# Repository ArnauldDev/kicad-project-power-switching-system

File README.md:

# Power switching system

Realization of a power supply board with four switches for switching between several power sources.

## Check list

- [x] Analysis of the specifications
- [x] Choice of components and case
- [x] Order components
- [x] Validation of the schematic
- [x] Definition of the PCB outline from the internal dimensions of the case
- [x] Validate component placement and lock footprints
- [x] Routing validation
- [x] Screen printing validation
- [x] Generating design files
- [x] Assembly of components on the PCB
- [x] Functional test of the electronic board and validation of the specifications
- [x] Integration of the electronic card in the case
- [x] Final test and document review
- [ ] Device delivery

---

## Tools used

### KiCad

[KiCad EDA - Schematic Capture & PCB Design Software](https://kicad-pcb.org/), version: 5.1.7

Open source EDA / electronics CAD software for Windows, macOS and Linux.

### FreeCAD - 3D parametric modeler

[FreeCAD](https://www.freecadweb.org/?lang=fr), version: 0.18.4

## Electrical diagram

---

## Integration into the housing

[Hammond 1599HGYBAT](https://www.hammfg.com/part/1599HGYBAT)

Enclosure - plastic, size: 220 mm x 110 mm x 44 mm (L x W x H)

## PCB outline, size: 213,00 mm x 96,60 mm (L x W), from FreeCAD

## Component placement and silk screen

|                        Placement                         |                      Silk screen                      |
| :------------------------------------------------------: | :---------------------------------------------------: |
|  |  |
|           F.Mask + Edge.Cuts + F.CrtYd + F.Fab           |                  F.SilkS + Edge.Cuts                  |

|                      Placement and Silk screen                      |
| :-----------------------------------------------------------------: |
|  |
|           F.SilkS + F.Mask + Edge.Cuts + F.CrtYd + F.Fab            |

<!--
### Component placement - Component layout

F.Mask + Edge.Cuts + F.CrtYd + F.Fab

### Silk screen

F.SilkS + Edge.Cuts
-->

## Top - Front Copper layer

<!--  -->

## Bottom - Back Copper layer

<!--  -->

<!-- ## Component layout

pcb-component-placement.pdf
 -->

## 3D rendering

## Integration of the electronic card in the case with the [FreeCAD](https://www.freecadweb.org) software

## Sectional view

## View of final STEP file for CNC

---

## [CHANGELOG](CHANGELOG.md)

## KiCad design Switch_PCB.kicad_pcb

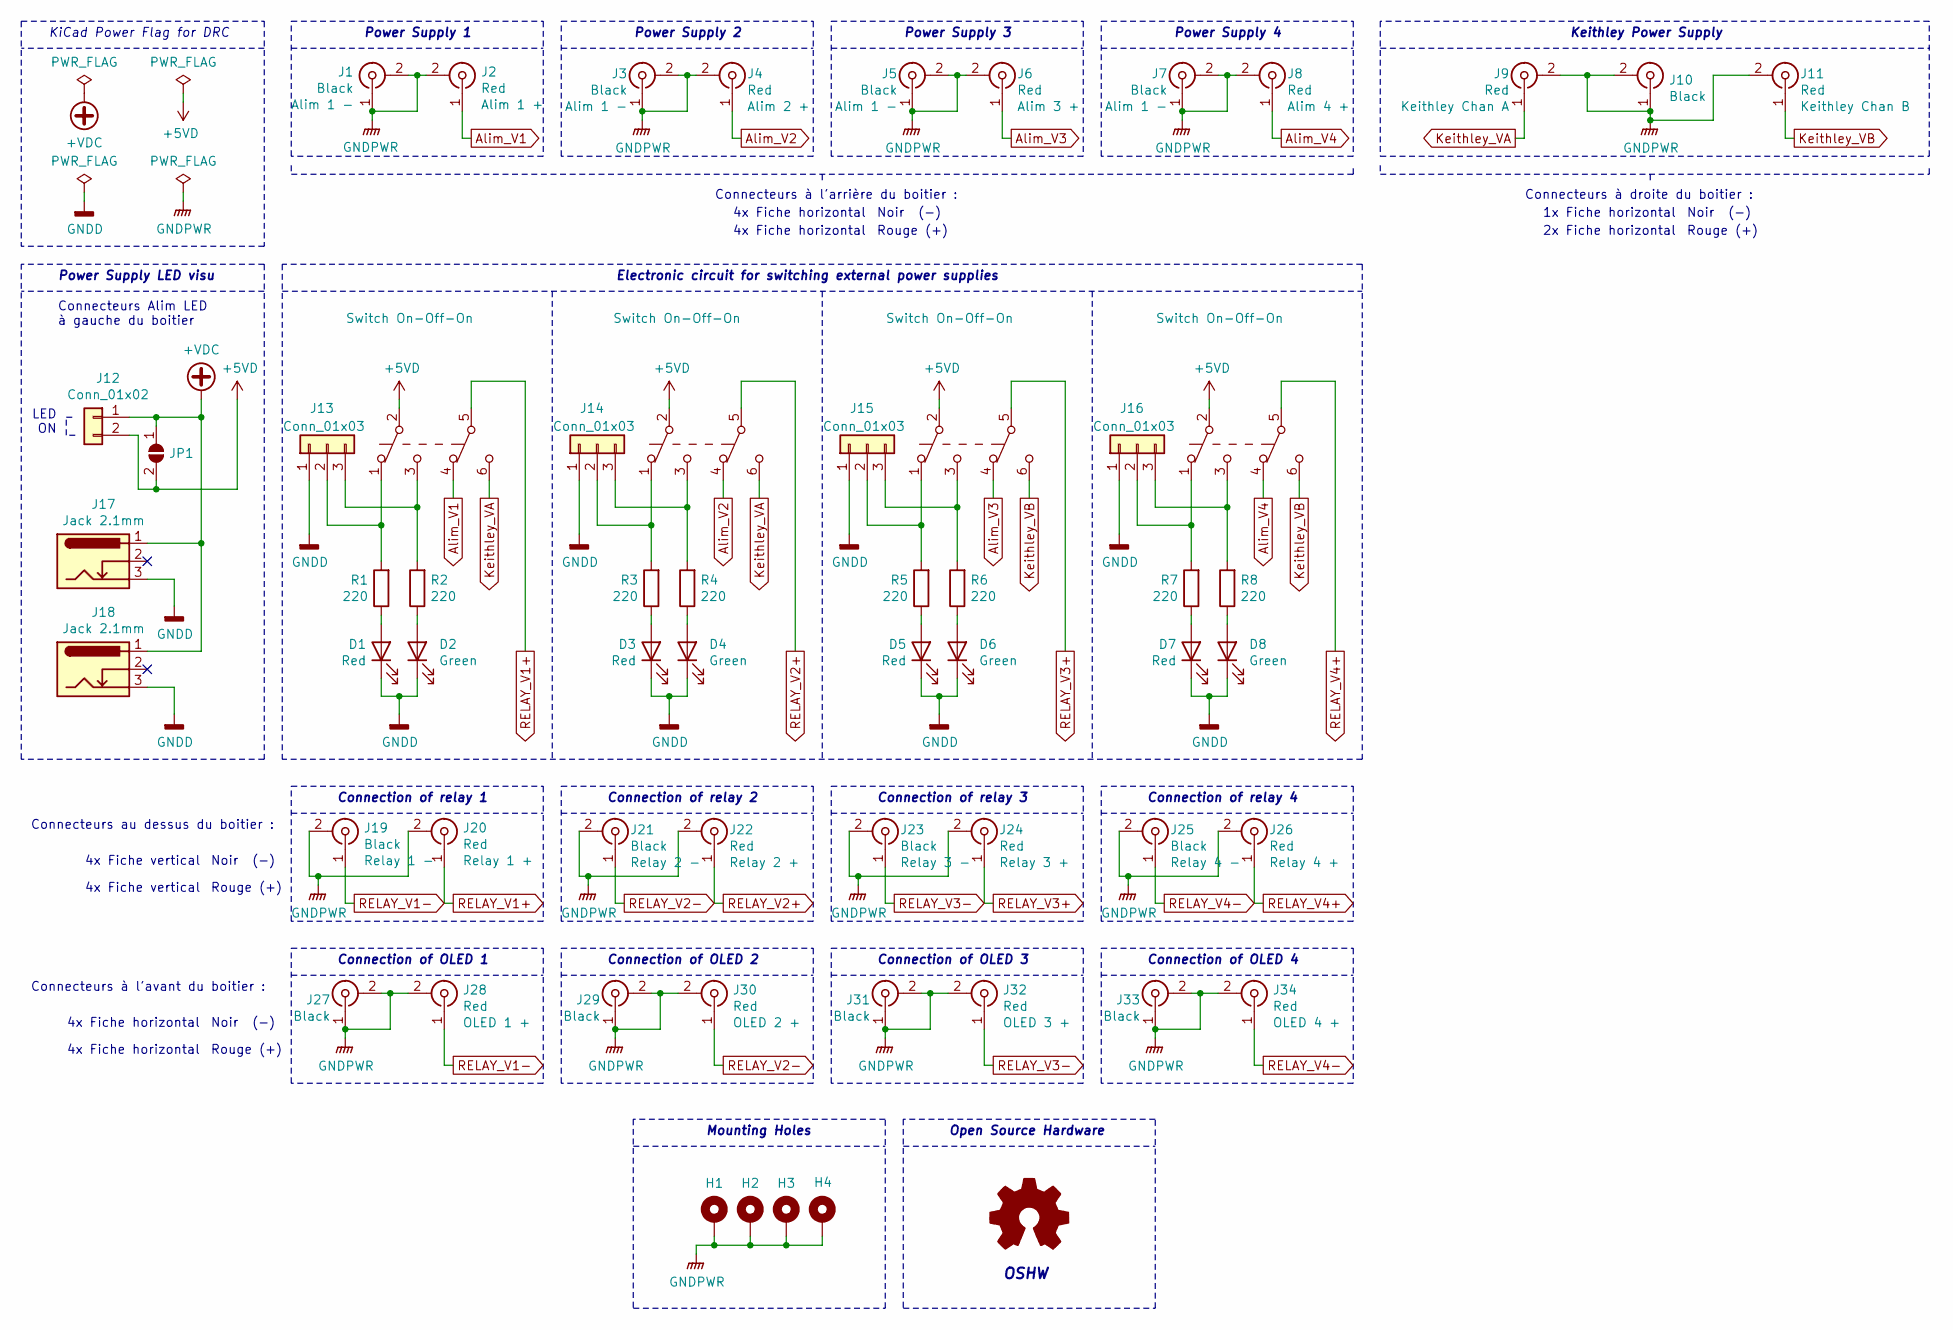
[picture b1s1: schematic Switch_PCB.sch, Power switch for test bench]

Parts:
D1, D3, D5, D7: Red; LED_D3.0mm_H18.0mm_Red; Manufacturer Part Number L-934ID
D2, D4, D6, D8: Green; LED_D3.0mm_H18.0mm_Green; Manufacturer Part Number L-934GD
H1, H2, H3, H4: MountingHole_Pad; MountingHole_3.2mm_M3_Pad
J1, J3, J5, J7, J10, J27, J29, J31, J33: Black; SCHUTZINGER_SWEB8094AU-SW_4mm_Horizontal_Black; Manufacturer Part Number SWEB 8094 Au / SW
J2, J4, J6, J8, J9, J11, J28, J30, J32, J34: Red; SCHUTZINGER_SWEB8094AU-RT_4mm_Horizontal_Red; Manufacturer Part Number SWEB 8094 Au / RT
J12: Conn_01x02; PinHeader_1x02_P2.54mm_Horizontal
J13, J14, J15, J16: Conn_01x03; PinHeader_1x03_P2.54mm_Vertical
J17, J18: Jack 2.1mm; BarrelJack_FC681465P_Pin3_Horizontal; Manufacturer Part Number FC681465P (DC-10LP)
J19, J21, J23, J25: Black; STAUBLI_66.9032-21_XELA-4_4mm_Vertical_Black; Manufacturer Part Number 66.9032-21
J20, J22, J24, J26: Red; STAUBLI_66.9032-22_XELA-4_4mm_Vertical_Red; Manufacturer Part Number 66.9032-22
JP1: SolderJumper_2_Open; SolderJumper-2_P1.3mm_Open_TrianglePad1.0x1.5mm
R1, R2, R3, R4, R5, R6, R7, R8: 220; R_1206_3216Metric_Pad1.30x1.75mm_HandSolder; Manufacturer Part Number CRG1206F220R
SW1, SW2, SW3, SW4: Switch On-Off-On; SW_TME_1MD3T1B1M1QE_DPDT_Straight; Manufacturer Part Number 1MD3T1B1M1QE

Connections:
+5VD: J12.2, JP1.2 (B), SW1.2 (B), SW2.2 (B), SW3.2 (B), SW4.2 (B)
+VDC: J12.1, J17.1, J18.1, JP1.1 (A)
Alim_V1: J2.1 (In), SW1.4 (A)
Alim_V2: J4.1 (In), SW2.4 (A)
Alim_V3: J6.1 (In), SW3.4 (A)
Alim_V4: J8.1 (In), SW4.4 (A)
GNDD: D1.1 (K), D2.1 (K), D3.1 (K), D4.1 (K), D5.1 (K), D6.1 (K), D7.1 (K), D8.1 (K), J13.1, J14.1, J15.1, J16.1, J17.3, J18.3
GNDPWR: H1.1, H2.1, H3.1, H4.1, J1.1 (In), J1.2 (Ext), J2.2 (Ext), J3.1 (In), J3.2 (Ext), J4.2 (Ext), J5.1 (In), J5.2 (Ext), J6.2 (Ext), J7.1 (In), J7.2 (Ext), J8.2 (Ext), J9.2 (Ext), J10.1 (In), J10.2 (Ext), J11.2 (Ext), J19.2 (Ext), J20.2 (Ext), J21.2 (Ext), J22.2 (Ext), J23.2 (Ext), J24.2 (Ext), J25.2 (Ext), J26.2 (Ext), J27.1 (In), J27.2 (Ext), J28.2 (Ext), J29.1 (In), J29.2 (Ext), J30.2 (Ext), J31.1 (In), J31.2 (Ext), J32.2 (Ext), J33.1 (In), J33.2 (Ext), J34.2 (Ext)
Keithley_VA: J9.1 (In), SW1.6 (C), SW2.6 (C)
Keithley_VB: J11.1 (In), SW3.6 (C), SW4.6 (C)
unnamed: D1.2 (A), R1.1
unnamed: D2.2 (A), R2.1
unnamed: D3.2 (A), R3.1
unnamed: D4.2 (A), R4.1
unnamed: D5.2 (A), R5.1
unnamed: D6.2 (A), R6.1
unnamed: D7.2 (A), R7.1
unnamed: D8.2 (A), R8.1
unnamed: J13.2, R1.2, SW1.1 (A)
unnamed: J13.3, R2.2, SW1.3 (C)
unnamed: J14.2, R3.2, SW2.1 (A)
unnamed: J14.3, R4.2, SW2.3 (C)
unnamed: J15.2, R5.2, SW3.1 (A)
unnamed: J15.3, R6.2, SW3.3 (C)
unnamed: J16.2, R7.2, SW4.1 (A)
unnamed: J16.3, R8.2, SW4.3 (C)
RELAY_V1+: J20.1 (In), SW1.5 (B)
RELAY_V1-: J19.1 (In), J28.1 (In)
RELAY_V2+: J22.1 (In), SW2.5 (B)
RELAY_V2-: J21.1 (In), J30.1 (In)
RELAY_V3+: J24.1 (In), SW3.5 (B)
RELAY_V3-: J23.1 (In), J32.1 (In)
RELAY_V4+: J26.1 (In), SW4.5 (B)
RELAY_V4-: J25.1 (In), J34.1 (In)

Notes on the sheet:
KiCad Power Flag for DRC
Keithley Power Supply
Power Supply 1
Power Supply 2
Power Supply 3
Power Supply 4
Connection of relay 1
Connection of relay 2
Connection of relay 3
Connection of relay 4
Connection of OLED 1
Connection of OLED 2
Connection of OLED 3
Connection of OLED 4
4x Fiche vertical
Rouge (+)
Noir (-)
Connecteurs au dessus du boitier :
Electronic circuit for switching external power supplies
Power Supply LED visu
Connecteurs à l'arrière du boitier :
4x Fiche horizontal
Connecteurs à l'avant du boitier :
Connecteurs à droite du boitier :
1x Fiche horizontal
2x Fiche horizontal
Connecteurs Alim LED à gauche du boitier
OSHW
Mounting Holes
Open Source Hardware
LED ON

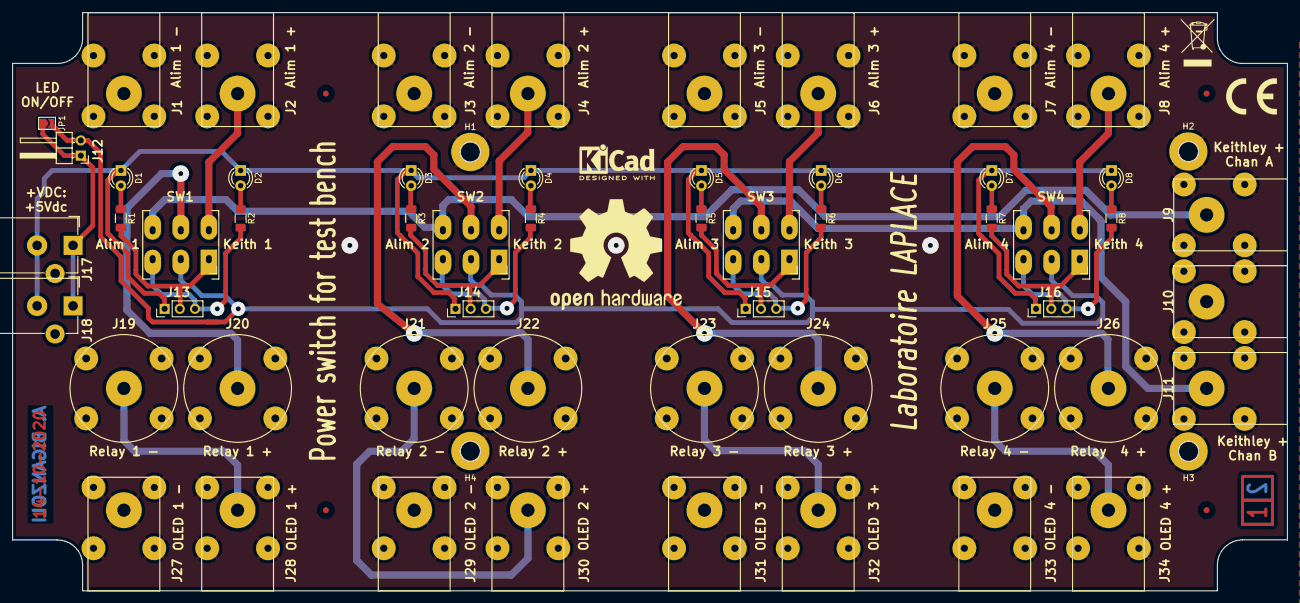
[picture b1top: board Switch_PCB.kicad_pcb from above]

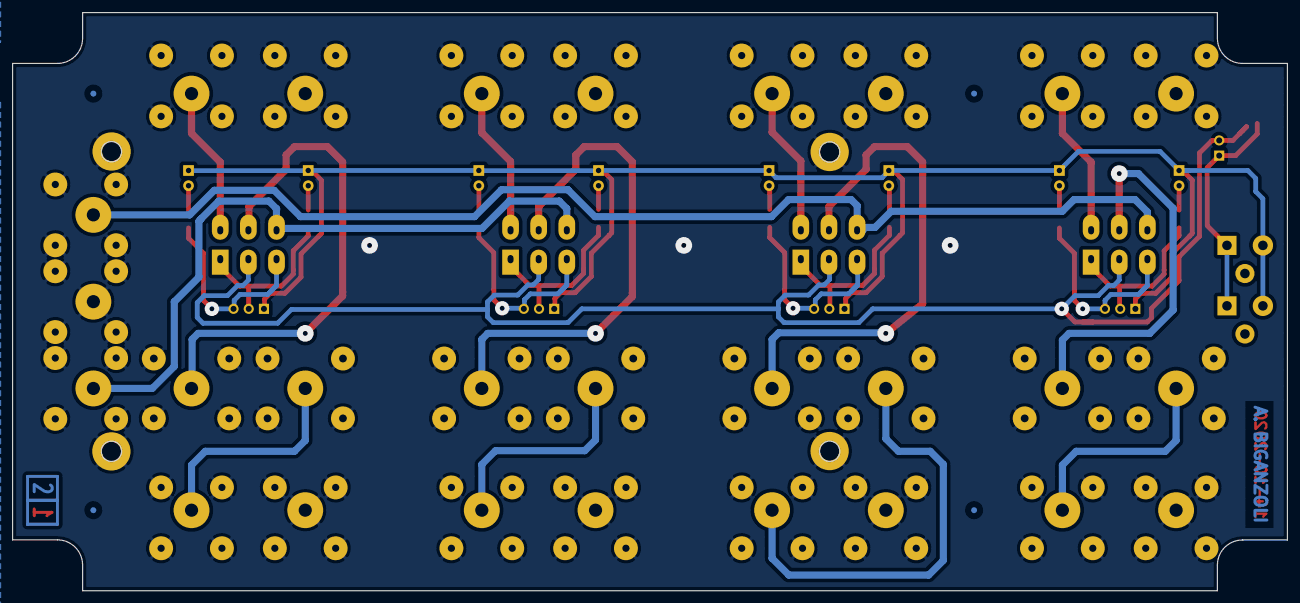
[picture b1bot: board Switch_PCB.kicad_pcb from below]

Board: 2 copper layers, 213.0 x 96.6 mm, 63 parts (2 on the bottom side), 34 nets.

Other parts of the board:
Ref**: L
Ref**#2, Ref**#3, Ref**#4: L

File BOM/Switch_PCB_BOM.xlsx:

Reference | Value | Footprint | Datasheet
R2 | 220 | Resistor_SMD:R_1206_3216Metric_Pad1.42x1.75mm_HandSolder | ~
R5 | 220 | Resistor_SMD:R_1206_3216Metric_Pad1.42x1.75mm_HandSolder | ~
R4 | 220 | Resistor_SMD:R_1206_3216Metric_Pad1.42x1.75mm_HandSolder | ~
R3 | 220 | Resistor_SMD:R_1206_3216Metric_Pad1.42x1.75mm_HandSolder | ~
R8 | 220 | Resistor_SMD:R_1206_3216Metric_Pad1.42x1.75mm_HandSolder | ~
R7 | 220 | Resistor_SMD:R_1206_3216Metric_Pad1.42x1.75mm_HandSolder | ~
R6 | 220 | Resistor_SMD:R_1206_3216Metric_Pad1.42x1.75mm_HandSolder | ~
R1 | 220 | Resistor_SMD:R_1206_3216Metric_Pad1.42x1.75mm_HandSolder | ~
J1 | Alim 1 + | ArnauldDev_Connector_Banana:SCHUTZINGER_SWEB8094AU-SW_4mm_Horizontal | ~
J16 | Alim 2 + | ArnauldDev_Connector_Banana:SCHUTZINGER_SWEB8094AU-SW_4mm_Horizontal | ~
J19 | Alim 3 + | ArnauldDev_Connector_Banana:SCHUTZINGER_SWEB8094AU-SW_4mm_Horizontal | ~
J32 | Alim 4 + | ArnauldDev_Connector_Banana:SCHUTZINGER_SWEB8094AU-SW_4mm_Horizontal | ~
J9 | Jack_5_Vdc | ArnauldDev_Connector_BarrelJack:BarrelJack_FC681465P_Pin3_Horizontal | ~
J8 | Keithley Chan A | ArnauldDev_Connector_Banana:SCHUTZINGER_SWEB8094AU-SW_4mm_Horizontal | ~
J26 | Keithley Chan B | ArnauldDev_Connector_Banana:SCHUTZINGER_SWEB8094AU-SW_4mm_Horizontal | ~
D1 | LED Alim 1 | LED_THT:LED_D3.0mm | https://docs.rs-online.com/c1ec/0900766b813955e9.pdf
D4 | LED Alim 2 | LED_THT:LED_D3.0mm | https://docs.rs-online.com/c1ec/0900766b813955e9.pdf
D5 | LED Alim 3 | LED_THT:LED_D3.0mm | https://docs.rs-online.com/c1ec/0900766b813955e9.pdf
D8 | LED Alim 4 | LED_THT:LED_D3.0mm | https://docs.rs-online.com/c1ec/0900766b813955e9.pdf
D2 | LED Keith 1 | LED_THT:LED_D3.0mm | https://docs.rs-online.com/5919/0900766b813955e6.pdf
D3 | LED Keith 2 | LED_THT:LED_D3.0mm | https://docs.rs-online.com/5919/0900766b813955e6.pdf
D6 | LED Keith 3 | LED_THT:LED_D3.0mm | https://docs.rs-online.com/5919/0900766b813955e6.pdf
D7 | LED Keith 4 | LED_THT:LED_D3.0mm | https://docs.rs-online.com/5919/0900766b813955e6.pdf
J7 | Masse - | ArnauldDev_Connector_Banana:SCHUTZINGER_SWEB8094AU-SW_4mm_Horizontal | ~
J13 | Masse - | ArnauldDev_Connector_Banana:SCHUTZINGER_SWEB8094AU-SW_4mm_Horizontal | ~
J10 | Masse - | ArnauldDev_Connector_Banana:SCHUTZINGER_SWEB8094AU-SW_4mm_Horizontal | ~
J2 | Masse - | ArnauldDev_Connector_Banana:SCHUTZINGER_SWEB8094AU-SW_4mm_Horizontal | ~
J11 | Masse - | ArnauldDev_Connector_Banana:SCHUTZINGER_SWEB8094AU-SW_4mm_Horizontal | ~
J4 | Masse - | ArnauldDev_Connector_Banana:SCHUTZINGER_SWEB8094AU-SW_4mm_Horizontal | ~
J14 | Masse - | ArnauldDev_Connector_Banana:SCHUTZINGER_SWEB8094AU-SW_4mm_Horizontal | ~
J20 | Masse - | ArnauldDev_Connector_Banana:SCHUTZINGER_SWEB8094AU-SW_4mm_Horizontal | ~
J24 | Masse - | ArnauldDev_Connector_Banana:SCHUTZINGER_SWEB8094AU-SW_4mm_Horizontal | ~
J3 | Masse - | ArnauldDev_Connector_Banana:SCHUTZINGER_SWEB8094AU-SW_4mm_Horizontal | ~
J12 | Masse - | ArnauldDev_Connector_Banana:SCHUTZINGER_SWEB8094AU-SW_4mm_Horizontal | ~
J18 | Masse - | ArnauldDev_Connector_Banana:SCHUTZINGER_SWEB8094AU-SW_4mm_Horizontal | ~
J22 | Masse - | ArnauldDev_Connector_Banana:SCHUTZINGER_SWEB8094AU-SW_4mm_Horizontal | ~
J6 | OLED 1 + | ArnauldDev_Connector_Banana:SCHUTZINGER_SWEB8094AU-SW_4mm_Horizontal | ~
J5 | OLED 1 + | ArnauldDev_Connector_Banana:SCHUTZINGER_SWEB8094AU-SW_4mm_Horizontal | ~
J15 | OLED 2 + | ArnauldDev_Connector_Banana:SCHUTZINGER_SWEB8094AU-SW_4mm_Horizontal | ~
J17 | OLED 2 + | ArnauldDev_Connector_Banana:SCHUTZINGER_SWEB8094AU-SW_4mm_Horizontal | ~
J23 | OLED 3 + | ArnauldDev_Connector_Banana:SCHUTZINGER_SWEB8094AU-SW_4mm_Horizontal | ~
J21 | OLED 3 + | ArnauldDev_Connector_Banana:SCHUTZINGER_SWEB8094AU-SW_4mm_Horizontal | ~
J30 | OLED 4 + | ArnauldDev_Connector_Banana:SCHUTZINGER_SWEB8094AU-SW_4mm_Horizontal | ~
J25 | OLED 4 + | ArnauldDev_Connector_Banana:SCHUTZINGER_SWEB8094AU-SW_4mm_Horizontal | ~
SW1 | Switch of Alim 1 | ArnauldDev_Button_Switch_THT:SW_TME_1MD3T1B1M1QE_DPDT_Straight | https://docs.rs-online.com/b84e/0900766b813ce699.pdf
SW2 | Switch of Alim 2 | ArnauldDev_Button_Switch_THT:SW_TME_1MD3T1B1M1QE_DPDT_Straight | https://docs.rs-online.com/b84e/0900766b813ce699.pdf
SW3 | Switch of Alim 3 | ArnauldDev_Button_Switch_THT:SW_TME_1MD3T1B1M1QE_DPDT_Straight | https://docs.rs-online.com/b84e/0900766b813ce699.pdf
SW4 | Switch of Alim 4 | ArnauldDev_Button_Switch_THT:SW_TME_1MD3T1B1M1QE_DPDT_Straight | https://docs.rs-online.com/b84e/0900766b813ce699.pdf

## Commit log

2020-09-24 Push the whole power switch project
2020-09-25 - validation schématique - validation du contour du PCB - validation du placement des composants, verrouillage des empreintes correctement positionnées
2020-09-26 Update color for each Banana connector to the pcb component placement 3d rendered.
2020-09-28 Update to ARNAULDDEV_SYS3DMOD global env var
2020-09-28 - Add 3 pin conn for LED states - Start of the routing of the tracks of the electronic card
2020-09-28 Duplicate tracks
2020-09-29 Screen printing validation
2020-09-30 Routing completed
2020-10-01 Add via to GNDPWR
2020-10-02 Project review and mechanical integration
2020-10-05 Update README files
2020-10-07 Create local components library
2020-10-07 Update local inter footprint SW_TME_1MD3T1B1M1QE_DPDT_Straight.kicad_mod, change for oblong hole. Add packages3D in kicad_local_mod folder.
2020-10-09 Change 3dshapes file name from (model ${ARNAULDDEV_SYS3DMOD}/ArnauldDev_ to (model ${KIPRJMOD}/kicad_local_mod/packages3d/
    kicad_local_mod/packages3d/ArnauldDev_Button_Switch_THT.3dshapes/SW_DPDT_11.43x12.70mm_W4.83mm_P4.70mm_Straight.step
    kicad_local_mod/packages3d/ArnauldDev_Button_Switch_THT.3dshapes/SW_DPDT_11.43x12.70mm_W4.83mm_P4.70mm_Straight.wrl
    kicad_local_mod/packages3d/ArnauldDev_Connector_Banana.3dshapes/SCHUTZINGER_SWEB8094AU-SW_4mm_Horizontal_Black.step
    kicad_local_mod/packages3d/ArnauldDev_Connector_Banana.3dshapes/SCHUTZINGER_SWEB8094AU-SW_4mm_Horizontal_Red.step
    kicad_local_mod/packages3d/ArnauldDev_Connector_Banana.3dshapes/STAUBLI_66.9032-21_XELA-4_4mm_Vertical_Black.step
2020-10-09 Update path for 3D modeles to packages3d Add fiducial marks in pcb
2020-10-10 Update project Add layers number
2020-10-11 Change the origin of SCHUTZINGER_SWEB8094AU-RT_4mm_Horizontal_Red.kicad_mod 3D model
2020-10-11 Change LED 3mm with 15.2mm Leads for 18 mm high * LED_D3.0mm_H18.0mm_Red * LED_D3.0mm_H18.0mm_Green
2020-10-14 Update mechanical integration
2020-11-02 Ajout des trous sur la face avant (voir le PB de rotation...)
2020-11-03 New drawing of front panel sketcher
2020-11-03 New housing box
2020-11-03 Holes in the front of the housing
2020-11-03 Draw on the side of the box for the Keithley power supply
2020-11-03 Drawing eight holes on the top side of the box
2020-11-03 Finalization of the integration of the electronic card in the box.
2020-11-03 Add image link and open it to a new windows
2020-11-03 Update links in Markdown files
